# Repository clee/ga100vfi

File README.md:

# PWMVID and GPU0 tools

This repository contains a PWMVID control-board design, STM32 firmware and host
tools, GA100 GPU0 register capture and analysis code, and an experiment-loop
description. Together they support board bring-up, PWM waveform experiments,
and checking how GPU register state changes after an attempt.

| Path | What it contains |
| --- | --- |
| [`hardware/`](hardware/README.md) | P8 KiCad schematic and PCB, test-pad map, and P9 assembly references |
| [`firmware/`](firmware/README.md) | STM32G431 application, custom USB bootloader, host utilities, and tests |
| [`driver/pwmvidctl/`](driver/pwmvidctl/README.md) | Operator CLI, sequence planner, calibration profiles, and waveform examples |
| [`gpu0-registers/`](gpu0-registers/README.md) | GA100 register maps, bounded capture engine, and offline state analysis |
| [`glitch-loop/`](glitch-loop/README.md) | Experiment-loop pseudocode and historical commanded waveforms |

## Offline checks

```sh
(cd firmware && sh tests/run_tests.sh && sh bootloader/tests/run_all.sh)
(cd driver/pwmvidctl && python3 -m unittest discover -s tests -v)
(cd gpu0-registers && cargo test --workspace --locked)
```

Building the STM32 images requires PlatformIO; see the firmware README for
build environments. Hardware bring-up requires the measurements in
[`firmware/docs/BENCH_ACCEPTANCE.md`](firmware/docs/BENCH_ACCEPTANCE.md).

Original project material is licensed under [MIT](LICENSE). Third-party terms
and source notices are described in [LICENSING.md](LICENSING.md).

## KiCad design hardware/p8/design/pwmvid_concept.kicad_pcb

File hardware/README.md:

# PWMVID board sources

Open [`p8/design/pwmvid_concept.kicad_pro`](p8/design/pwmvid_concept.kicad_pro)
in KiCad 9 for the schematic and PCB. The design directory includes its custom
symbols and footprints. [`p8/docs/testpad-key.csv`](p8/docs/testpad-key.csv)
maps the exposed probe points to nets and board coordinates.

[`p9/`](p9/README.md) contains the customer hand-fit BOM, placement file,
and rotation corrections. P9 uses P8 copper and retains the P8 silkscreen.
The schematic specifies STM32G431CBT6 as U1 for the 128 KiB firmware. Check
the fitted part and boot configuration on an assembled board.

The [P8 expansion note](p8/P8_EXPANSION_AND_TESTPOINTS.md) describes J9, test
pads, and electrical limits. Firmware qualification steps are in the
[bench checklist](../firmware/docs/BENCH_ACCEPTANCE.md).

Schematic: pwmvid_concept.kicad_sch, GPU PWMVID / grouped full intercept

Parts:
C2, C4, C5, C6, C7, C8, C9, C11, C19, C20, C21, C24, C25, C34, C35, C36, C37, C40, C41, C42, C46: 100n; C_0603_1608Metric; MPN CC0603KRX7R9BB104; LCSC C14663
C12, C33: 1u; C_0603_1608Metric; MPN CL10A105KB8NNNC; LCSC C15849
C13: 100n reset; C_0603_1608Metric; MPN CC0603KRX7R9BB104; LCSC C14663
C14: 100p ADC provisional; C_0603_1608Metric; MPN 0603CG101J500NT; LCSC C1635
C15: DNP COMP filter; C_0603_1608Metric; not fitted
C16, C17: 2u2 50V X7R CL31B225KBHNNNE; C_1206_3216Metric; MPN CL31B225KBHNNNE; LCSC C50254
C18: 100n USB ESD VBUS; C_0603_1608Metric; MPN CC0603KRX7R9BB104; LCSC C14663
C22, C23: 470p C0G 5% timeout QUALIFY; C_0603_1608Metric; MPN 0603CG471J500NT; LCSC C36252
C28: DNP sense filter; C_0603_1608Metric; not fitted
C30: 1u local LDO input; C_0603_1608Metric; MPN CL10A105KB8NNNC; LCSC C15849
C31: 4u7 50V X7R CL31B475KBHNNNE; C_1206_3216Metric; MPN CL31B475KBHNNNE; LCSC C51205
C32: 1u 50V X5R; C_0603_1608Metric; MPN CL10A105KB8NNNC; LCSC C15849
C43, C44: 18p C0G TUNE; C_0603_1608Metric; MPN CL10C180JB8NNNC; LCSC C1647
D1: MHTC197CRGBCT C3028844; LED_MHTC197CRGBCT; MPN MHTC197CRGBCT; LCSC C3028844
D2: PMEG2010EA,115 SERIES; D_SOD-323; MPN PMEG2010EA,115; LCSC C193668
D3: PMEG2010EA,115 CATCH; D_SOD-323; MPN PMEG2010EA,115; LCSC C193668
J1: GPU I/O: 4 wires + GND pads; Wire4plusGND_1p2mm_3mm
J6: DNP OPTIONAL SWD HEADER; PinHeader_1x04_P2.54mm_Vertical; not fitted
J7: NRST GND; WirePair_1p2mm_3mm
J8: HRO TYPE-C-31-M-12 C165948; TYPE-C-31-M-12_C165948_JLC_0p25_Ring; MPN TYPE-C-31-M-12; LCSC C165948
J9: DNP EXPANSION / 3V3 GPIO + RAIL OUTPUTS; PinHeader_2x04_P2.54mm_Vertical; not fitted
JP1: ARM RELEASE / OPEN; SolderJumper-2_P1.3mm_Open_Pad1.0x1.5mm
Q1: MMBT3904 COMP trip; SOT-23; MPN MMBT3904(RANGE:100-300); LCSC C20526
Q2: MMBT3904 OE SINK; SOT-23; MPN MMBT3904(RANGE:100-300); LCSC C20526
R1: 33R tune SI; R_0603_1608Metric; MPN 0603WAF330JT5E; LCSC C23140
R2: 2k2 default disable / OE slew; R_0603_1608Metric; MPN 0603WAF2201T5E; LCSC C4190
R3: 0R VDDA same supervised rail; R_0603_1608Metric; MPN 0603WAF0000T5E; LCSC C21189
R4: 10k reset; R_0603_1608Metric; MPN 0603WAF1002T5E; LCSC C25804
R5: 10k 1% ADC sense; R_0603_1608Metric; MPN 0603WAF1002T5E; LCSC C25804
R6: 10k 1% COMP sense; R_0603_1608Metric; MPN 0603WAF1002T5E; LCSC C25804
R7: 10k VBUS bleed; R_0603_1608Metric; MPN 0603WAF1002T5E; LCSC C25804
R8: 10k ADC divider; R_0603_1608Metric; MPN 0603WAF1002T5E; LCSC C25804
R9: 10k COMP divider; R_0603_1608Metric; MPN 0603WAF1002T5E; LCSC C25804
R11, R12: 10k 1% timeout QUALIFY; R_0603_1608Metric; MPN 0603WAF1002T5E; LCSC C25804
R13, R14: 10k 0.1% 25ppm OVP sense; R_0603_1608Metric; MPN RT0603BRD0710KL; LCSC C95204
R16: 8k45 0.1% 25ppm OVP upper; R_0603_1608Metric; MPN RT0603BRD078K45L; LCSC C861590
R17: 10k 0.1% 25ppm OVP lower; R_0603_1608Metric; MPN RT0603BRD0710KL; LCSC C95204
R18: 100k 0.1% 25ppm OVP lower; R_0603_1608Metric; MPN RT0603BRD07100KL; LCSC C122538
R22: 10k HOST_ARM_RAW default low; R_0603_1608Metric; MPN 0603WAF1002T5E; LCSC C25804
R23: 100k external break defined; R_0603_1608Metric; MPN 0603WAF1003T5E; LCSC C25803
R25: 10k; R_0603_1608Metric; MPN 0603WAF1002T5E; LCSC C25804
R26: 47k B E; R_0603_1608Metric; MPN 0603WAF4702T5E; LCSC C25819
R27: 10k healthy pullup; R_0603_1608Metric; MPN 0603WAF1002T5E; LCSC C25804
R28: 10k HARD assembly inhibit; R_0603_1608Metric; MPN 0603WAF1002T5E; LCSC C25804
R36: 0R HSE drive TUNE; R_0603_1608Metric; MPN 0603WAF0000T5E; LCSC C21189
R37: 5k1 1% CC1 Rd; R_0603_1608Metric; MPN 0603WAF5101T5E; LCSC C23186
R38: 5k1 1% CC2 Rd; R_0603_1608Metric; MPN 0603WAF5101T5E; LCSC C23186
R39: 10k OE base; R_0603_1608Metric; MPN 0603WAF1002T5E; LCSC C25804
R40: 47k OE off; R_0603_1608Metric; MPN 0603WAF4702T5E; LCSC C25819
R41: 10k HOST_PERMIT_RAW default off; R_0603_1608Metric; MPN 0603WAF1002T5E; LCSC C25804
R42: 10k LOCAL1V8 bleed; R_0603_1608Metric; MPN 0603WAF1002T5E; LCSC C25804
R43, R44, R45: 1k LED current QUALIFY; R_0603_1608Metric; MPN 0603WAF1001T5E; LCSC C21190
R46, R47, R48: 100k LED default off; R_0603_1608Metric; MPN 0603WAF1003T5E; LCSC C25803
R49: 47k 1% RUN readback isolation; R_0603_1608Metric; MPN 0603WAF4702T5E; LCSC C25819
R50: 1k PWM source default LOW; R_0603_1608Metric; MPN 0603WAF1001T5E; LCSC C21190
R90: 100R 1% OUTPUT DAMPING; R_0603_1608Metric; MPN 0603WAF1000T5E; LCSC C22775
TP1: GPU_PWM_1V8; TestPoint_Pad_D1.5mm
TP2: VRM_PWM_1V8; TestPoint_Pad_D1.5mm
TP3: PWM_TIM1_3V3; TestPoint_Pad_D1.5mm
TP4: Keystone5003 ORANGE NV; TestPoint_Keystone_5000-5004_Miniature; MPN 5003; LCSC C238124
TP5: Keystone5004 YELLOW FAULT; TestPoint_Keystone_5000-5004_Miniature; MPN 5004; LCSC C2906762
TP6: Keystone5000 RED 3V3; TestPoint_Keystone_5000-5004_Miniature; MPN 5000; LCSC C5199900
TP7: Keystone5000 RED 1V8; TestPoint_Keystone_5000-5004_Miniature; MPN 5000; LCSC C5199900
TP8: Keystone5116 GREEN RUN; TestPoint_Keystone_5000-5004_Miniature; MPN 5116; LCSC C2938788
TP9: Keystone5001 BLACK GND; TestPoint_Keystone_5000-5004_Miniature; MPN 5001; LCSC C238122
TP10, TP11, TP12: GND; TestPoint_Pad_D1.5mm
TP13: Keystone5117 BLUE COMP; TestPoint_Keystone_5000-5004_Miniature; MPN 5117; LCSC C5224552
TP14: Keystone5002 WHITE NRST; TestPoint_Keystone_5000-5004_Miniature; MPN 5002; LCSC C238123
TP15: Keystone5000 RED VBUS; TestPoint_Keystone_5000-5004_Miniature; MPN 5000; LCSC C5199900
TP16: REF1V25 PROBE; TestPoint_Pad_D1.0mm
TP17: OVP_THRESHOLD PROBE; TestPoint_Pad_D1.0mm
TP18: HOST_ARM_RAW PROBE; ProbePad_D1.0mm_Courtyard1.5mm
TP19: HOST_ARM PROBE; ProbePad_D1.0mm_Courtyard1.5mm
TP20: HOST_PERMIT_RAW PROBE; ProbePad_D1.0mm_Courtyard1.5mm
TP21: HOST_PERMIT PROBE; ProbePad_D1.0mm_Courtyard1.5mm
TP22: CONFIG_VALID PROBE; ProbePad_D1.0mm_Courtyard1.5mm
TP23: RESET_OK PROBE; ProbePad_D1.0mm_Courtyard1.5mm
TP24: COMP_OK_FAST PROBE; ProbePad_D1.0mm_Courtyard1.5mm
TP25: OVP_OK PROBE; ProbePad_D1.0mm_Courtyard1.5mm
TP26: RISE_RECENT PROBE; ProbePad_D1.0mm_Courtyard1.5mm
TP27: FALL_RECENT PROBE; ProbePad_D1.0mm_Courtyard1.5mm
TP28: EDGE_OVP_OK PROBE; ProbePad_D1.0mm_Courtyard1.5mm
TP29: SYSTEM_OK PROBE; ProbePad_D1.0mm_Courtyard1.5mm
TP30: HEALTH_CLEAR_N PROBE; ProbePad_D1.0mm_Courtyard1.5mm
TP31: HARD_CLEAR_N PROBE; ProbePad_D1.0mm_Courtyard1.5mm
TP32: SYNTH_OE_N PROBE; ProbePad_D1.0mm_Courtyard1.5mm
TP33: USB_REG_IN PROBE; ProbePad_D1.0mm_Courtyard1.5mm
TP34, TP35, TP36: GND PROBE; ProbePad_D1.0mm_Courtyard1.5mm
U1: STM32G431CBT6; LQFP-48_7x7mm_P0.5mm; MPN STM32G431CBT6; LCSC C529354
U2: SN74AUP1T17DCKR GPU CAPTURE; SOT-353_SC-70-5; MPN SN74AUP1T17DCKR; LCSC C2652100
U3: SN74AUP1T17DCKR VRM CAPTURE; SOT-353_SC-70-5; MPN SN74AUP1T17DCKR; LCSC C2652100
U4: 74AUP1G125GW; SOT-353_SC-70-5; MPN 74AUP1G125GW,125; LCSC C478136
U5: USBLC6-2SC6; SOT-23-6; MPN USBLC6-2SC6; LCSC C7519
U6: TLV75533PDRVR 3V3; WSON-6-1EP_2x2mm_P0.65mm_TI_EP_Paste_0p125; MPN TLV75533PDRVR; LCSC C2861750
U7: SN74LVC3G17DCUR EDGE CONDITION; VSSOP-8_2.3x2mm_P0.5mm; MPN SN74LVC3G17DCUR; LCSC C68245
U8: TMUX1511PWR; TSSOP-14_4.4x5mm_P0.65mm; MPN TMUX1511PWR; LCSC C2866750
U9: TLV3201AIDBVR EXTERNAL OVP; SOT-23-5; MPN TLV3201AIDBVR; LCSC C105188
U10: SN74LVC1G123DCUR PRE-DRIVER RISE; VSSOP-8_2.3x2mm_P0.5mm; MPN SN74LVC1G123DCUR; LCSC C352969
U11: SN74LVC1G123DCUR PRE-DRIVER FALL; VSSOP-8_2.3x2mm_P0.5mm; MPN SN74LVC1G123DCUR; LCSC C352969
U14: TPS70918DRVRM3 LOCAL 1V8; WSON-6-1EP_2x2mm_P0.65mm_TI_EP_Paste_0p125; MPN TPS70918DRVRM3; LCSC C2864751
U15: REF3312AIDBZR; SOT-23; MPN REF3312AIDBZR; LCSC C183104
U16: SN74LVC1G11DBVR EDGE AND OVP; SOT-23-6; MPN SN74LVC1G11DBVR; LCSC C22046
U17: SN74LVC1G11DBVR RESET AND COMP; SOT-23-6; MPN SN74LVC1G11DBVR; LCSC C22046
U18: SN74LVC1G11DBVR ASYNC CLEAR; SOT-23-6; MPN SN74LVC1G11DBVR; LCSC C22046
U19: SN74LVC1G74DCUR HOST ARM; VSSOP-8_2.3x2mm_P0.5mm; MPN SN74LVC1G74DCUR; LCSC C70285
U21: TPS3808G33DBVR 3V3 RESET; SOT-23-6; MPN TPS3808G33DBVR; LCSC C43698
U22: TPS3808G18DBVR 1V8 RESET; SOT-23-6; MPN TPS3808G18DBVR; LCSC C129330
U23: SN74LVC1G08DBVR HOST PERMIT; SOT-23-5; MPN SN74LVC1G08DBVR; LCSC C7666
U24: SN74LVC2G17DBVR HOST EDGES; SOT-23-6; MPN SN74LVC2G17DBVR; LCSC C10429
Y1: 8MHz YXC X32258MOB4SI C2682775; Crystal_SMD_3225-4Pin_3.2x2.5mm; MPN X32258MOB4SI; LCSC C2682775

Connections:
/1V8_IO: C5.1, C31.1, J9.6, R2.1, R42.1, TP7.1, U4.5 (VCC 1V8), U14.1 (OUT), U22.5 (SENSE)
/3V3: C2.1, C4.1, C6.1, C7.1, C8.1, C9.1, C17.1, C19.1, C20.1, C21.1, C24.1, C25.1, C30.1, C32.1, C34.1, C35.1, C36.1, C37.1, C40.1, C41.1, C42.1, C46.1, D3.2 (A), J6.1, J9.4, JP1.1 (A), R3.1, R4.1, R11.1, R12.1, R27.1, TP6.1, U1.1 (VBAT), U1.24 (VDD), U1.36 (VDD), U1.48 (VDD), U2.5 (VCC), U3.5 (VCC), U6.1 (OUT), U7.8 (VCC), U8.14 (VDD), U9.5 (VCC), U10.8 (VCC), U11.2 (B rising), U11.8 (VCC), U14.6 (IN), U15.1 (IN), U16.5 (VCC), U17.5 (VCC), U18.5 (VCC), U19.2 (D), U19.7 (/PRE), U19.8 (VCC), U21.3 (/MR), U21.5 (SENSE), U21.6 (VDD), U22.3 (/MR), U22.6 (VDD), U23.5 (VCC), U24.5 (VCC)
/ADC_SWITCH_IN: R5.2, U8.2 (S1 ADC)
/COMP2_OK: Q1.3 (C), R27.2, U7.6 (3A)
/COMP2_OVP: R25.1, TP13.1, U1.15 (PA7)
/COMP_OK_FAST: TP24.1, U7.2 (3Y), U17.6 (C)
/COMP_SWITCH_IN: R6.2, U8.5 (S2 COMP)
/COMP_TRIP_BASE: Q1.1 (B), R25.2, R26.1
/CONFIG_VALID: JP1.2 (B), R28.1, TP22.1, U18.6 (C)
/EDGE_OVP_OK: TP28.1, U16.4 (Y), U18.1 (A)
/EXT_PA5: J9.3, U1.13 (PA5)
/EXT_PB0: J9.1, U1.16 (PB0)
/EXT_PB10: J9.5, U1.22 (PB10)
/EXT_PB11: J9.7, U1.25 (PB11)
/FALL_CEXT: C23.1, U11.6 (Cext)
/FALL_RC: C23.2, R12.2, U11.7 (Rext/Cext)
/FALL_RECENT: TP27.1, U11.5 (Q valid edge), U16.6 (C)
/FAULT_NORUN: TP5.1, U19.3 (/Q FAULT)
/GND: C2.2, C4.2, C5.2, C6.2, C7.2, C8.2, C9.2, C11.2, C12.2, C13.2, C14.2, C15.2, C16.2, C17.2, C18.2, C19.2, C20.2, C21.2, C24.2, C25.2, C28.2, C30.2, C31.2, C32.2, C33.2, C34.2, C35.2, C36.2, C37.2, C40.2, C41.2, C42.2, C43.2, C44.2, C46.2, D1.4 (K), J1.4, J1.5, J1.6, J6.2, J7.2, J8.A1 (GND), J8.A12 (GND), J8.B1 (GND), J8.B12 (GND), J8.S1 (SHIELD), J9.8, Q1.2 (E), Q2.2 (E), R7.2, R8.2, R9.2, R14.2, R17.2, R18.2, R22.2, R23.2, R26.2, R28.2, R37.2, R38.2, R40.2, R41.2, R42.2, R46.2, R47.2, R48.2, R50.2, TP9.1, TP10.1, TP11.1, TP12.1, TP34.1, TP35.1, TP36.1, U1.19 (VSSA), U1.23 (VSS), U1.35 (VSS), U1.47 (VSS), U2.3 (GND), U3.3 (GND), U4.3 (GND), U5.2 (GND), U6.3 (GND), U6.7 (EP GND), U7.4 (GND), U8.7 (GND), U8.13 (SEL4), U9.2 (GND), U10.1 (A falling), U10.4 (GND), U11.4 (GND), U14.3 (GND), U14.7 (EP GND), U15.3 (GND), U16.2 (GND), U17.2 (GND), U18.2 (GND), U19.4 (GND), U21.2 (GND), U22.2 (GND), U23.3 (GND), U24.2 (GND), Y1.2, Y1.4
/GPU_CAPTURE_3V3: U1.8 (PA0), U2.4 (Y 3V3)
/GPU_PWM_1V8: J1.1, TP1.1, U2.2 (A VBUS tolerant)
/HARD_CLEAR_N: TP31.1, U19.6 (/CLR hardfault), U23.4
/HEALTH_CLEAR_N: TP30.1, U18.4 (Y), U23.1
/HOST_ARM: TP19.1, U19.1 (CLK host arm), U24.6 (1Y)
/HOST_ARM_RAW: R22.1, TP18.1, U1.29 (PB15), U24.1 (1A)
/HOST_PERMIT: TP21.1, U23.2, U24.4 (2Y)
/HOST_PERMIT_RAW: R41.1, TP20.1, U1.17 (PB1), U24.3 (2A)
/HSE_SERIES: C44.1, R36.2, Y1.3
/LED_B_A: D1.2 (BA), R45.2
/LED_G_A: D1.1 (GA), R44.2
/LED_R_A: D1.3 (RA), R43.2
/NRST: C13.1, J7.1, R4.2, TP14.1, U1.7 (PG10), U7.3 (2A), U21.1 (/RESET OD), U22.1 (/RESET OD)
/NVVDD_ADC: C14.1, R8.1, U1.10 (PA2), U8.3 (D1 ADC)
/NVVDD_COMP: C15.1, R9.1, U1.11 (PA3), U8.6 (D2 COMP)
/NVVDD_SENSE: J1.3, R5.1, R6.1, R13.1, TP4.1
/OE_BASE: Q2.1 (B), R39.2, R40.1
/OSC_IN: C43.1, U1.5 (PF0), Y1.1
/OSC_OUT: R36.1, U1.6 (PF1)
/OVP_OK: R23.1, TP25.1, U1.26 (PB12), U9.1 (OUT OVP_OK), U16.1 (A)
/OVP_THRESHOLD: R16.2, R17.1, R18.1, TP17.1, U9.3 (IN+ THRESH)
/PWM_DAMPED: R1.2, U4.2 (A 3V3 tolerant)
/PWM_TIM1_3V3: R1.1, R50.1, TP3.1, U1.30 (PA8), U10.2 (B rising), U11.1 (A falling)
/REF1V25: C33.1, R16.1, TP16.1, U15.2 (OUT 1V25)
/RESET_OK: TP23.1, U7.5 (2Y), U8.1 (SEL1), U8.4 (SEL2), U8.10 (SEL3), U10.3 (/CLR), U11.3 (/CLR), U17.1 (A)
/RISE_CEXT: C22.1, U10.6 (Cext)
/RISE_RC: C22.2, R11.2, U10.7 (Rext/Cext)
/RISE_RECENT: TP26.1, U10.5 (Q valid edge), U16.3 (B)
/RUN_PERMISSION: R39.1, R49.1, TP8.1, U19.5 (Q RUN)
/RUN_SENSE: R49.2, U1.28 (PB14)
/SAFE_NV_SENSE: C28.1, R14.1, U8.8 (D3), U9.4 (IN- SENSE)
/SAFE_SENSE_IN: R13.2, U8.9 (S3)
/STATUS_B: R45.1, R48.1, U1.27 (PB13)
/STATUS_G: R44.1, R47.1, U1.32 (PA10)
/STATUS_R: R43.1, R46.1, U1.31 (PA9)
/SWCLK: J6.4, U1.38 (PA14)
/SWDIO: J6.3, U1.37 (PA13)
/SYNTH_OE_N: Q2.3 (C), R2.2, TP32.1, U4.1 (/OE)
/SYNTH_PWM_1V8: R90.1, U4.4 (Y 1V8)
/SYSTEM_OK: TP29.1, U17.4 (Y), U18.3 (B)
/USB_CC1: J8.A5 (CC1), R37.1
/USB_CC2: J8.B5 (CC2), R38.1
/USB_DM: J8.A7 (D-), J8.B7 (D-), U1.33 (PA11), U5.1 (IO1 connector), U5.6 (IO1 MCU)
/USB_DP: J8.A6 (D+), J8.B6 (D+), U1.34 (PA12), U5.3 (IO2 connector), U5.4 (IO2 MCU)
/USB_REG_IN: C16.1, D2.1 (K), D3.1 (K), TP33.1, U6.4 (EN), U6.6 (IN)
/USB_VBUS: C18.1, D2.2 (A), J8.A4 (VBUS), J8.A9 (VBUS), J8.B4 (VBUS), J8.B9 (VBUS), J9.2, R7.1, TP15.1, U5.5 (VBUS), U7.1 (1A)
/VBUS_DETECT: U1.42 (PB5), U7.7 (1Y), U17.3 (B)
/VDDA: C11.1, C12.1, R3.2, U1.20 (VREF+), U1.21 (VDDA)
/VRM_CAPTURE_3V3: U1.14 (PA6), U3.4 (Y 3V3)
/VRM_PWM_1V8: J1.2, R90.2, TP2.1, U3.2 (A VBUS tolerant)

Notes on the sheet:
MCU / capture, synthesis, USB device
Clock / MCU analog and digital decoupling
USB-C / USB power and VBUS presence
Local 1.8 V / shared rail supervision
Four GPU connections / capture channels
Default-off output / real VRM-node feedback
NVVDD sensing / three branches, shared U8
External threshold / OVP / internal trip out
Pre-output rising / falling edge watchdogs
Health gates / reset-dominant RUN latch
Host ARM / async DISARM / status
Probe hooks and waveform / ground pads
GPU PWMVID / P8 PRODUCTION REVIEW / BENCH RELEASE REQUIRED
Four GPU wires; remove GPU_R30. Hi-Z assumes MP2888A-equivalent behavior. No passive bypass or 1.5 V guarantee.
Sense and precision OVP network fitted; JP1 OPEN is the assembly inhibit. Firmware not implemented.
Dotted regions are editable native KiCad graphics. Net labels connect groups; no firmware-transparent pass-through.
J9: unbuffered 3.3 V GPIO only Rails are outputs; no external backpower GPIOs reset analog / no pull DNP header; firmware support required
Local debug probe pads / high impedance measurement only / no external drive

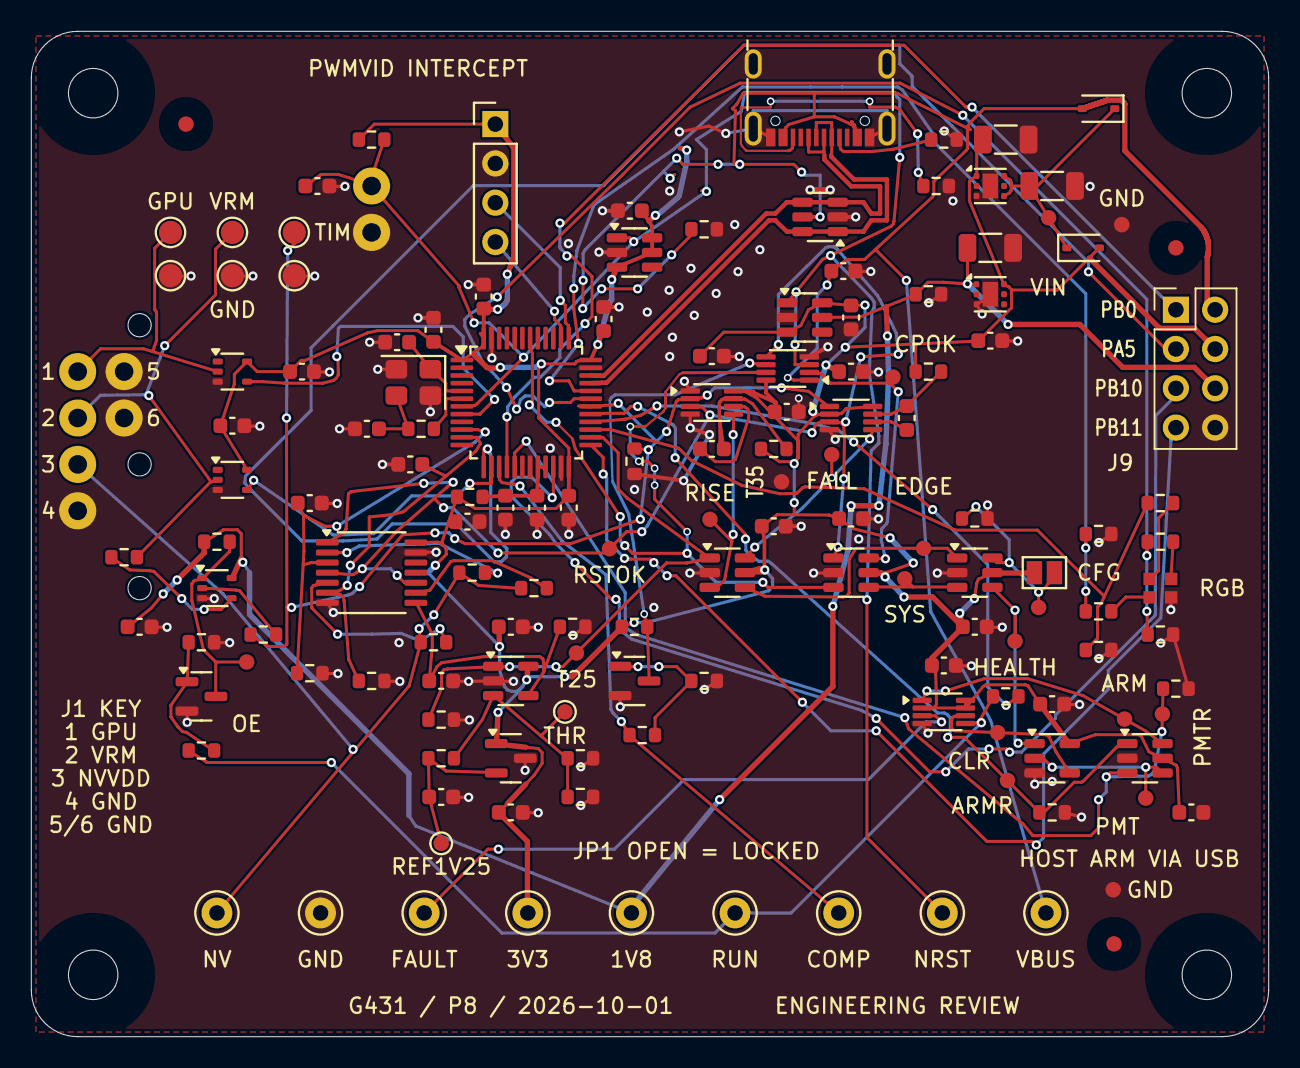
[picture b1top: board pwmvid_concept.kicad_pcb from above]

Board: 2 copper layers, 80.0 x 65.0 mm, 154 parts (0 on the bottom side), 69 nets.

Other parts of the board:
FID1, FID2, FID3: Fiducial_1mm_Mask3mm
H1, H2, H3: Strain relief 1.5mm NPTH
H4, H5, H6, H7: M3 / 3.2mm NPTH; MountingHole_3.2mm_M3
